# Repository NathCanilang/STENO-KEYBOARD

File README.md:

# Steno-Keyboard Firmware

High-performance firmware for RP2040/RP2350 based stenography keyboards, built using the Raspberry Pi Pico SDK and TinyUSB.

## Features

- **Matrix Scanning**: Efficient 11x6 matrix scanning implementation.
- **HID Protocol**: Custom 4-byte (27-key) HID bitmap reports for NKRO (N-Key Rollover) support.
- **Debouncing**: Eager debouncing logic for minimal latency.
- **USB Stack**: Integrated TinyUSB for lightweight HID communication.

## Project Structure

- [Steno-Keyboard.c](Steno-Keyboard.c): Main entry point and hardware initialization.
- [keyboard.c](keyboard.c): Matrix scanning and HID report generation logic.
- [usb_descriptors.c](usb_descriptors.c): USB descriptor definitions.
- [sys_debounce/](sys_debounce/): Core debouncing implementation.

## Getting Started

### Prerequisites

- [Raspberry Pi Pico SDK](https://github.com/raspberrypi/pico-sdk)
- CMake (3.13+)
- Ninja or Make build system

### Build Instructions

1. Create and enter the build directory:
   ```bash
   mkdir build
   cd build
   ```

2. Generate build files:
   ```bash
   cmake ..
   ```

3. Compile the project:
   ```bash
   ninja
   ```

4. Flash the `Steno-Keyboard.uf2` file to the device.

## Technical Notes

- **HID Buffer Size**: The HID report buffer is configured to 32 bytes to accommodate the custom bitmap structure.
- **Chord Collection**: Implements a buffer collection mechanism to ensure synchronized delivery of stenographic chords.
- **SDK Usage**: Utilizes native Pico SDK hardware APIs for optimal performance.

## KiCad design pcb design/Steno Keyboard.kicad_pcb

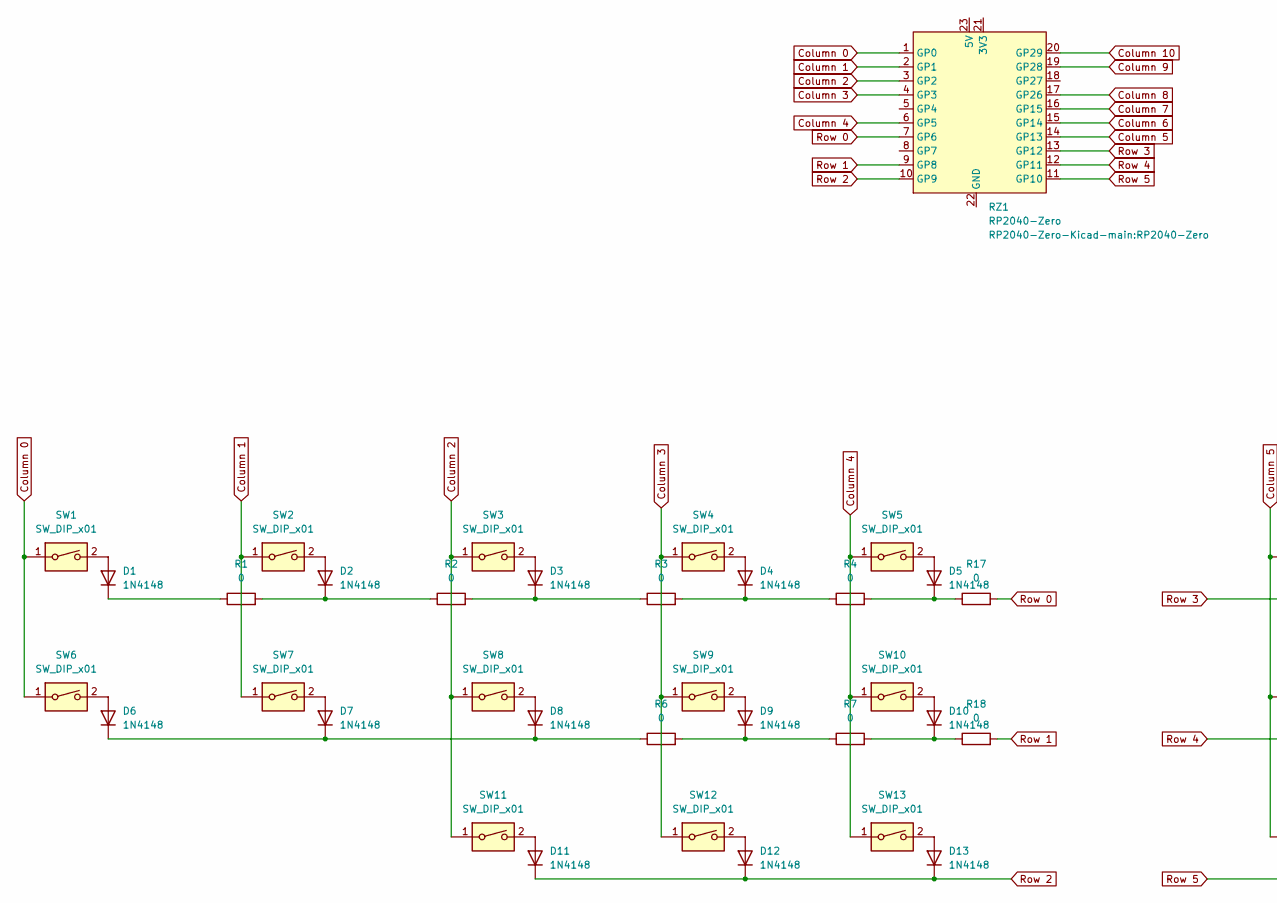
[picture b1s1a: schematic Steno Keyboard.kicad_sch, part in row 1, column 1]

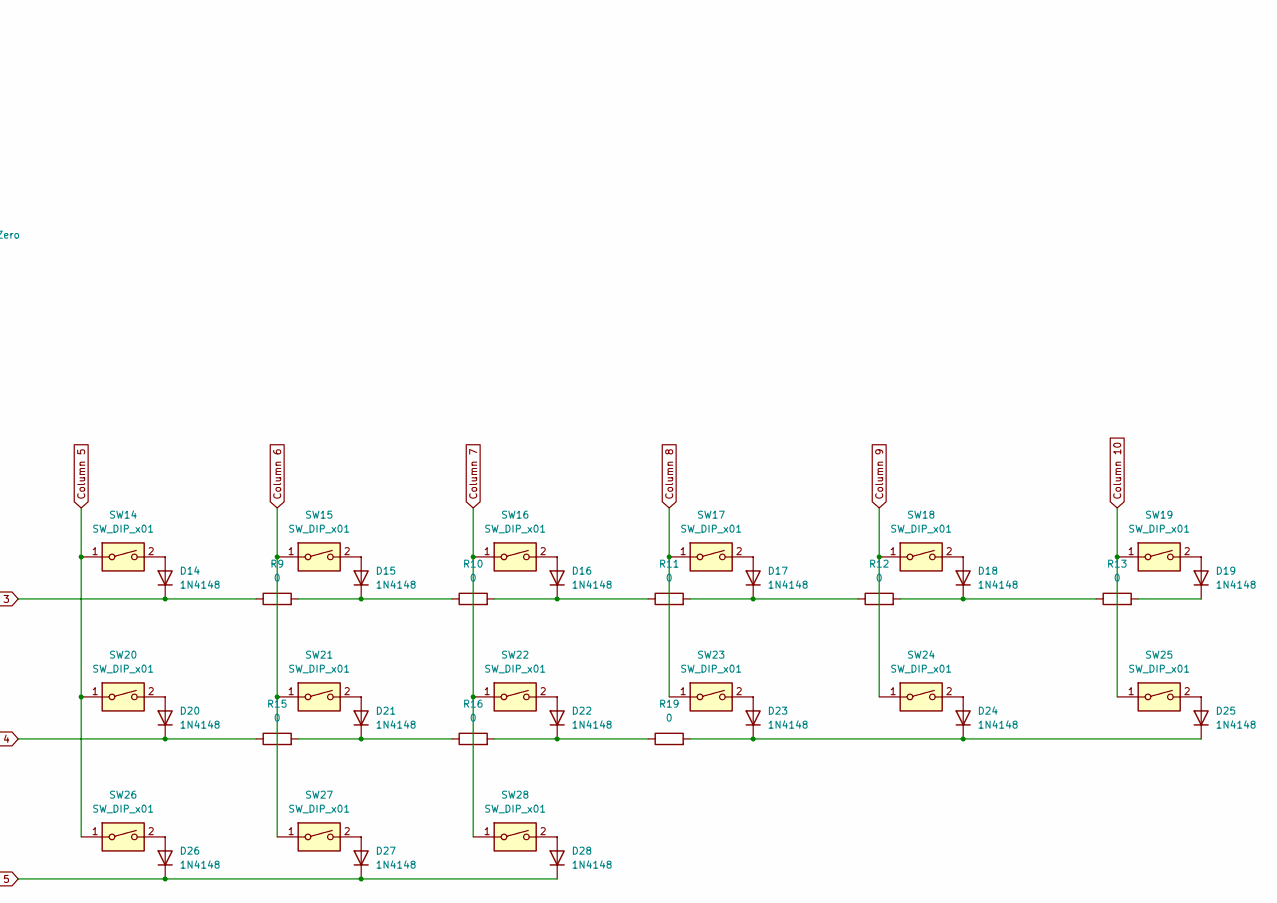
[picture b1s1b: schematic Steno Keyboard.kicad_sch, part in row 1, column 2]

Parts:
D1, D2, D3, D4, D5, D6, D7, D8, D9, D10, D11, D12, D13, D14, D15, D16, D17, D18, D19, D20, D21, D22, D23, D24, D25, D26, D27, D28: 1N4148; D_SOD-123
R1, R2, R3, R4, R6, R7, R9, R10, R11, R12, R13, R15, R16, R17, R18, R19: 0; R_1206_3216Metric_Pad1.30x1.75mm_HandSolder
RZ1: RP2040-Zero
SW1, SW2, SW3, SW4, SW5, SW6, SW7, SW8, SW9, SW10, SW11, SW12, SW13, SW14, SW15, SW16, SW17, SW18, SW19, SW20, SW21, SW22, SW23, SW24, SW25, SW26, SW27, SW28: SW_DIP_x01; Kailh_socket_MX

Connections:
Column 0: RZ1.1 (GP0), SW1.1, SW6.1
Column 1: RZ1.2 (GP1), SW2.1, SW7.1
Column 2: RZ1.3 (GP2), SW3.1, SW8.1, SW11.1
Column 3: RZ1.4 (GP3), SW4.1, SW9.1, SW12.1
Column 4: RZ1.6 (GP5), SW5.1, SW10.1, SW13.1
Column 5: RZ1.14 (GP13), SW14.1, SW20.1, SW26.1
Column 6: RZ1.15 (GP14), SW15.1, SW21.1, SW27.1
Column 7: RZ1.16 (GP15), SW16.1, SW22.1, SW28.1
Column 8: RZ1.17 (GP26), SW17.1, SW23.1
Column 9: RZ1.19 (GP28), SW18.1, SW24.1
Column 10: RZ1.20 (GP29), SW19.1, SW25.1
unnamed: D1.2 (A), SW1.2
unnamed: D1.1 (K), R1.1
unnamed: D2.2 (A), SW2.2
unnamed: D2.1 (K), R1.2, R2.1
unnamed: D3.2 (A), SW3.2
unnamed: D3.1 (K), R2.2, R3.1
unnamed: D4.2 (A), SW4.2
unnamed: D4.1 (K), R3.2, R4.1
unnamed: D5.2 (A), SW5.2
unnamed: D5.1 (K), R4.2, R17.1
unnamed: D6.2 (A), SW6.2
unnamed: D6.1 (K), D7.1 (K), D8.1 (K), R6.1
unnamed: D7.2 (A), SW7.2
unnamed: D8.2 (A), SW8.2
unnamed: D9.2 (A), SW9.2
unnamed: D9.1 (K), R6.2, R7.1
unnamed: D10.2 (A), SW10.2
unnamed: D10.1 (K), R7.2, R18.1
unnamed: D11.2 (A), SW11.2
unnamed: D12.2 (A), SW12.2
unnamed: D13.2 (A), SW13.2
unnamed: D14.2 (A), SW14.2
unnamed: D15.2 (A), SW15.2
unnamed: D15.1 (K), R9.2, R10.1
unnamed: D16.2 (A), SW16.2
unnamed: D16.1 (K), R10.2, R11.1
unnamed: D17.2 (A), SW17.2
unnamed: D17.1 (K), R11.2, R12.1
unnamed: D18.2 (A), SW18.2
unnamed: D18.1 (K), R12.2, R13.1
unnamed: D19.2 (A), SW19.2
unnamed: D19.1 (K), R13.2
unnamed: D20.2 (A), SW20.2
unnamed: D21.2 (A), SW21.2
unnamed: D21.1 (K), R15.2, R16.1
unnamed: D22.2 (A), SW22.2
unnamed: D22.1 (K), R16.2, R19.1
unnamed: D23.2 (A), SW23.2
unnamed: D23.1 (K), D24.1 (K), D25.1 (K), R19.2
unnamed: D24.2 (A), SW24.2
unnamed: D25.2 (A), SW25.2
unnamed: D26.2 (A), SW26.2
unnamed: D27.2 (A), SW27.2
unnamed: D28.2 (A), SW28.2
Row 0: R17.2, RZ1.7 (GP6)
Row 1: R18.2, RZ1.9 (GP8)
Row 2: D11.1 (K), D12.1 (K), D13.1 (K), RZ1.10 (GP9)
Row 3: D14.1 (K), R9.1, RZ1.13 (GP12)
Row 4: D20.1 (K), R15.1, RZ1.12 (GP11)
Row 5: D26.1 (K), D27.1 (K), D28.1 (K), RZ1.11 (GP10)

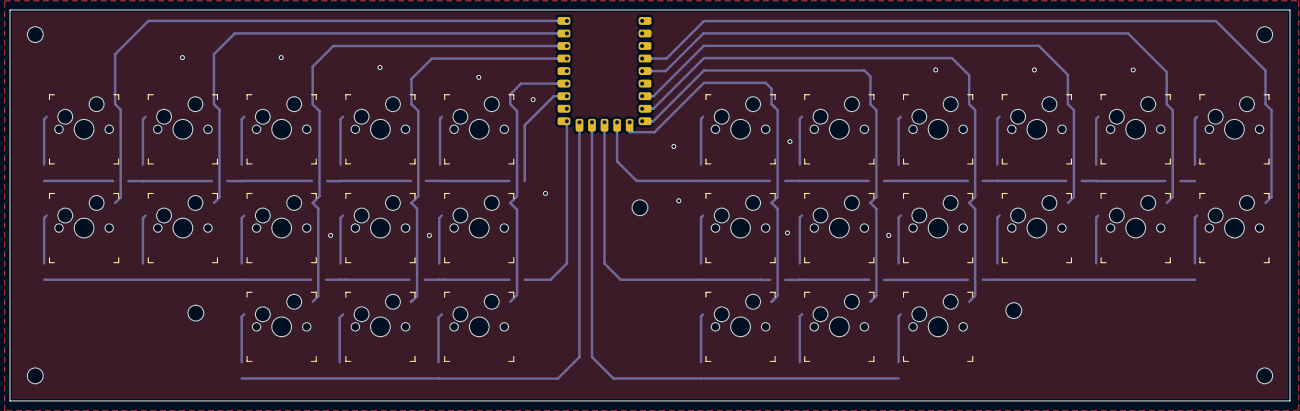
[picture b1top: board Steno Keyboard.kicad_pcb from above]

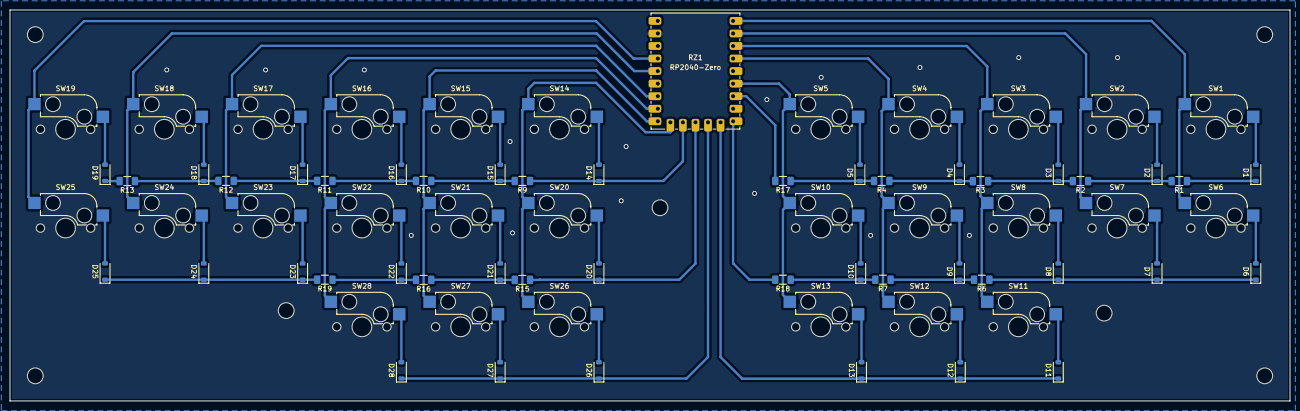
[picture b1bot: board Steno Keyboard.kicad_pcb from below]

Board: 2 copper layers, 259.2 x 79.2 mm, 73 parts (45 on the bottom side), 61 nets.

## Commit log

2026-06-01 created the basic firmware
2026-06-01 Fix: added the firmware
2026-06-03 added debounce logic
2026-06-03 improved the debounce logic a bit
2026-06-06 updated PCB design
2026-06-07 major rewrite for logic for testable logic purposes
2026-06-10 added unit tests
2026-06-10 fixed the keyboard_task logic by rewriting it
2026-06-17 rewrite complete, debounce is still flawed
2026-06-17 need to fix the byte sending
2026-06-21 flawed logic. will do rewrite
2026-06-24 fixing the debouncing and code architecture
2026-06-25 bugs and logic fixes
